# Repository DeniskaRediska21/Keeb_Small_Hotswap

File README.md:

# Split Ergo Ortholinear Hotswap Keyboard 

This project attempts to create easelly reproducible split ortholinear  hotswap mechanical
keyboard. 

Gimmics: 
+ This design doesn't require any diodes
+ Uses PiPico as MC, runs on CircuitPython
+ Key layouts are changed by dragging a file onto PiPicos storrage
+ Halves are connected through TypeC
+ PCB fits into 100x100mm square, so it is very cheap to order from chineese manifacturers

# Gallery

|  |  |
|------------------------------|-------------------------|

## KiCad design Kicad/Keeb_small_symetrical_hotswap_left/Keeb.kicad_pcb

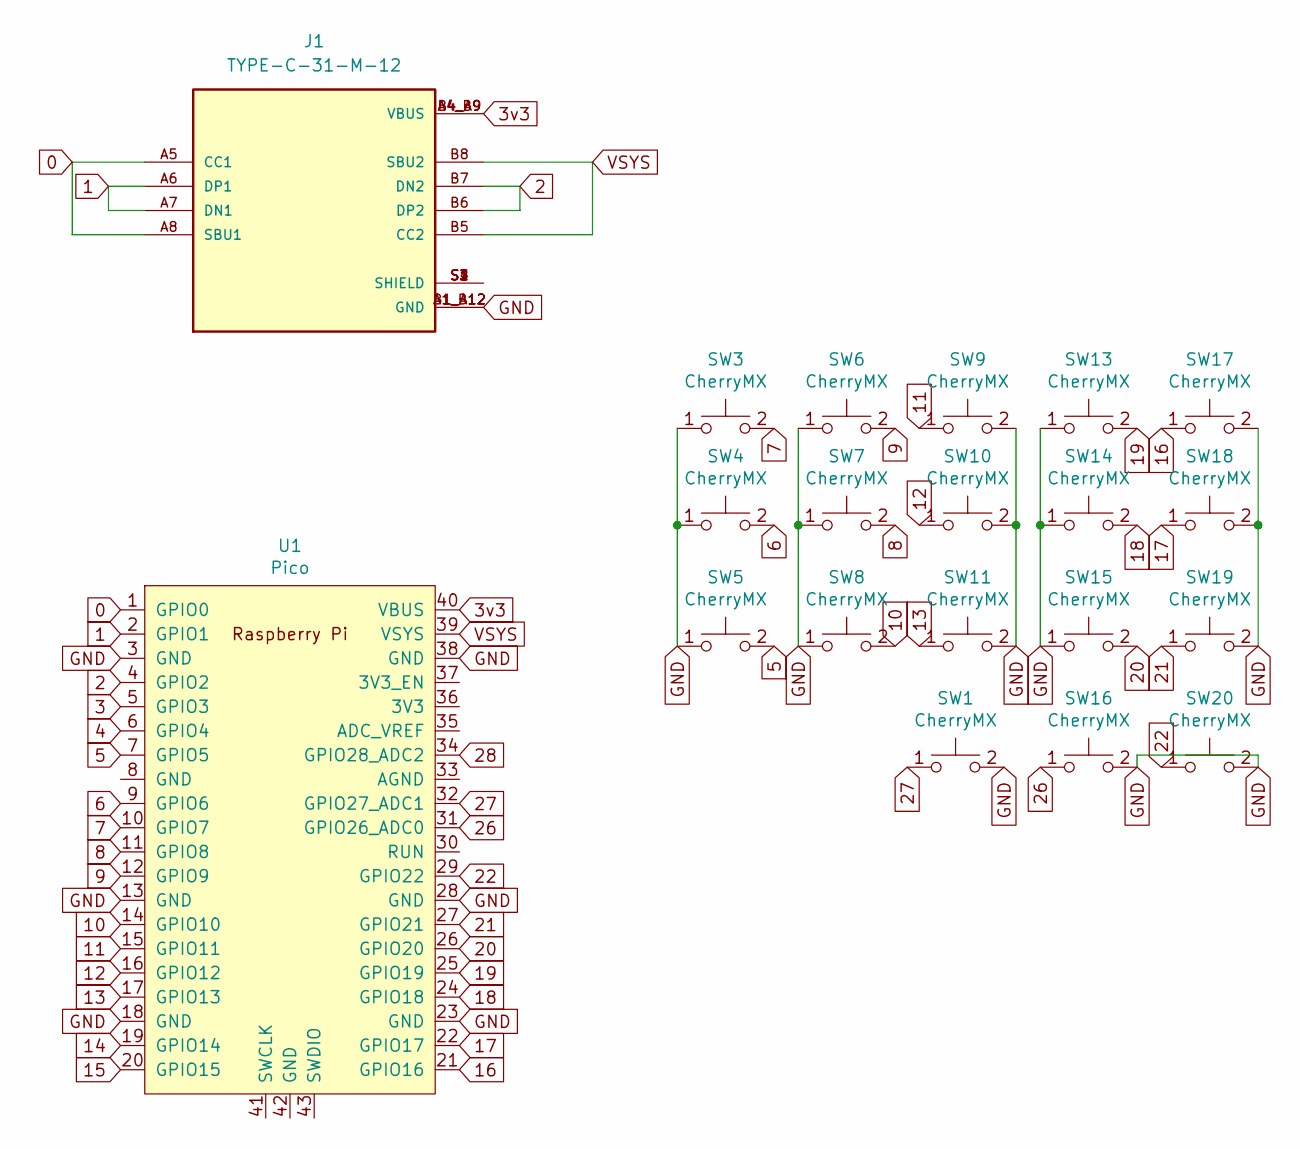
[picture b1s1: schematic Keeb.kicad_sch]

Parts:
J1: TYPE-C-31-M-12; HRO_TYPE-C-31-M-12; PARTREV 2020.12.08
SW1, SW3, SW4, SW5, SW6, SW7, SW8, SW9, SW10, SW11, SW13, SW14, SW15, SW16, SW17, SW18, SW19, SW20: CherryMX; Hotswap_MX_1.00u
U1: Pico; RPi_Pico_SMD_TH_NO_HOLES

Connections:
0: J1.A5 (CC1), J1.A8 (SBU1), U1.1 (GPIO0)
1: J1.A6 (DP1), J1.A7 (DN1), U1.2 (GPIO1)
2: J1.B6 (DP2), J1.B7 (DN2), U1.4 (GPIO2)
3: U1.5 (GPIO3)
3v3: J1.A4_B9 (VBUS), J1.B4_A9 (VBUS), U1.40 (VBUS)
4: U1.6 (GPIO4)
5: SW5.2, U1.7 (GPIO5)
6: SW4.2, U1.9 (GPIO6)
7: SW3.2, U1.10 (GPIO7)
8: SW7.2, U1.11 (GPIO8)
9: SW6.2, U1.12 (GPIO9)
10: SW8.2, U1.14 (GPIO10)
11: SW9.1, U1.15 (GPIO11)
12: SW10.1, U1.16 (GPIO12)
13: SW11.1, U1.17 (GPIO13)
14: U1.19 (GPIO14)
15: U1.20 (GPIO15)
16: SW17.1, U1.21 (GPIO16)
17: SW18.1, U1.22 (GPIO17)
18: SW14.2, U1.24 (GPIO18)
19: SW13.2, U1.25 (GPIO19)
20: SW15.2, U1.26 (GPIO20)
21: SW19.1, U1.27 (GPIO21)
22: SW20.1, U1.29 (GPIO22)
26: SW16.1, U1.31 (GPIO26_ADC0)
27: SW1.1, U1.32 (GPIO27_ADC1)
28: U1.34 (GPIO28_ADC2)
GND: J1.A1_B12 (GND), J1.B1_A12 (GND), SW1.2, SW3.1, SW4.1, SW5.1, SW6.1, SW7.1, SW8.1, SW9.2, SW10.2, SW11.2, SW13.1, SW14.1, SW15.1, SW16.2, SW17.2, SW18.2, SW19.2, SW20.2, U1.3 (GND), U1.13 (GND), U1.18 (GND), U1.23 (GND), U1.28 (GND), U1.38 (GND)
unnamed: J1.S1 (SHIELD), J1.S2 (SHIELD), J1.S3 (SHIELD), J1.S4 (SHIELD)
VSYS: J1.B5 (CC2), J1.B8 (SBU2), U1.39 (VSYS)

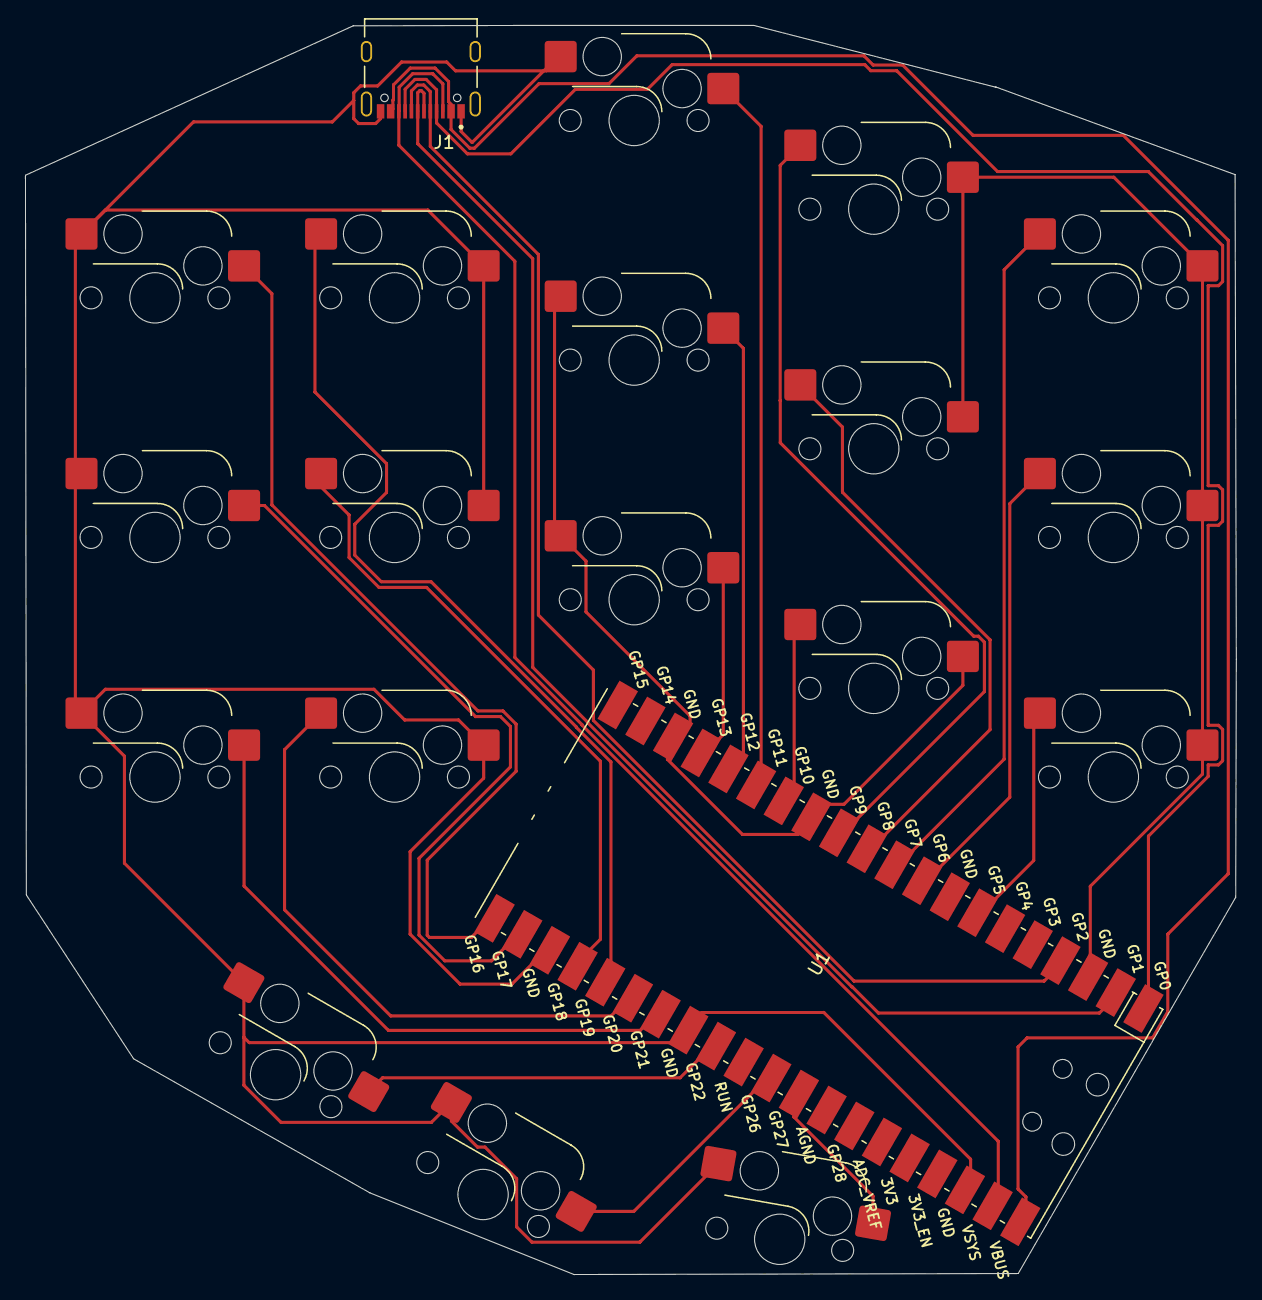
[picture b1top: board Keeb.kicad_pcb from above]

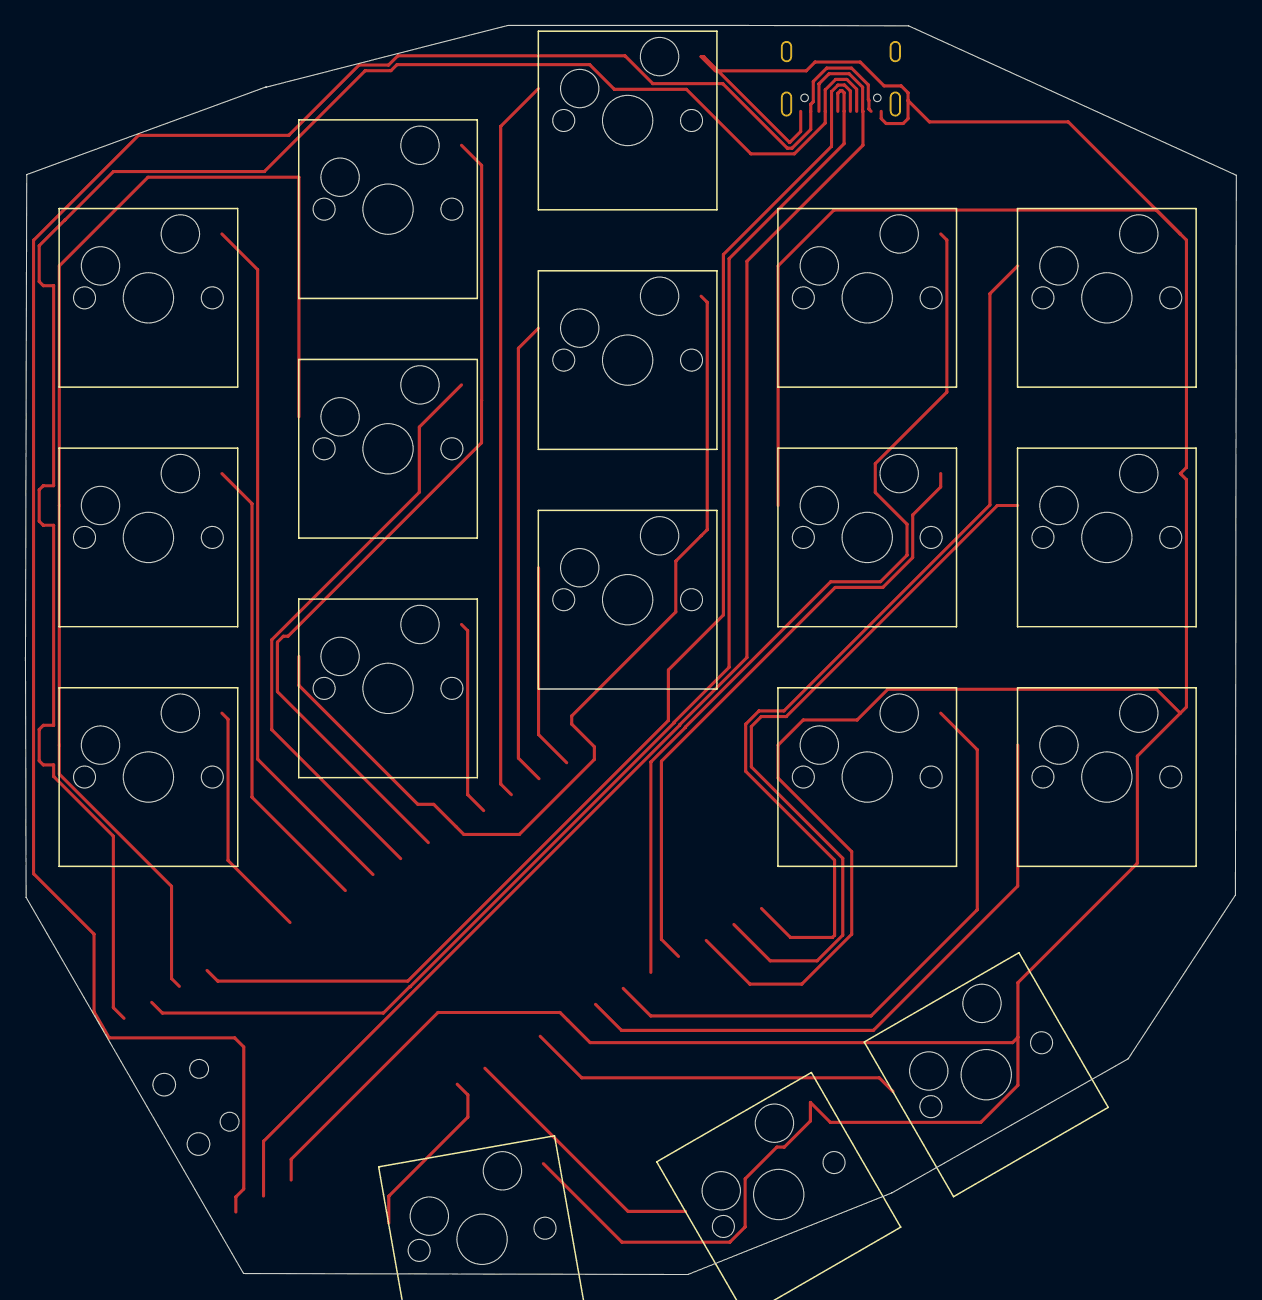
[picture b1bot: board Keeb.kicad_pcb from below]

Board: 2 copper layers, 96.3 x 99.3 mm, 20 parts (18 on the bottom side), 25 nets.

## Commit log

2023-11-27 done some routing
2023-11-28 More or less MVP of left keabord PCB
2023-11-28 Started work on the right half, fixed routing in the left half
2023-11-28 MVP of the right half
2023-11-28 rm holes for controller
2023-11-28 Added mounting holes to the PCB
2023-11-28 added Readme
